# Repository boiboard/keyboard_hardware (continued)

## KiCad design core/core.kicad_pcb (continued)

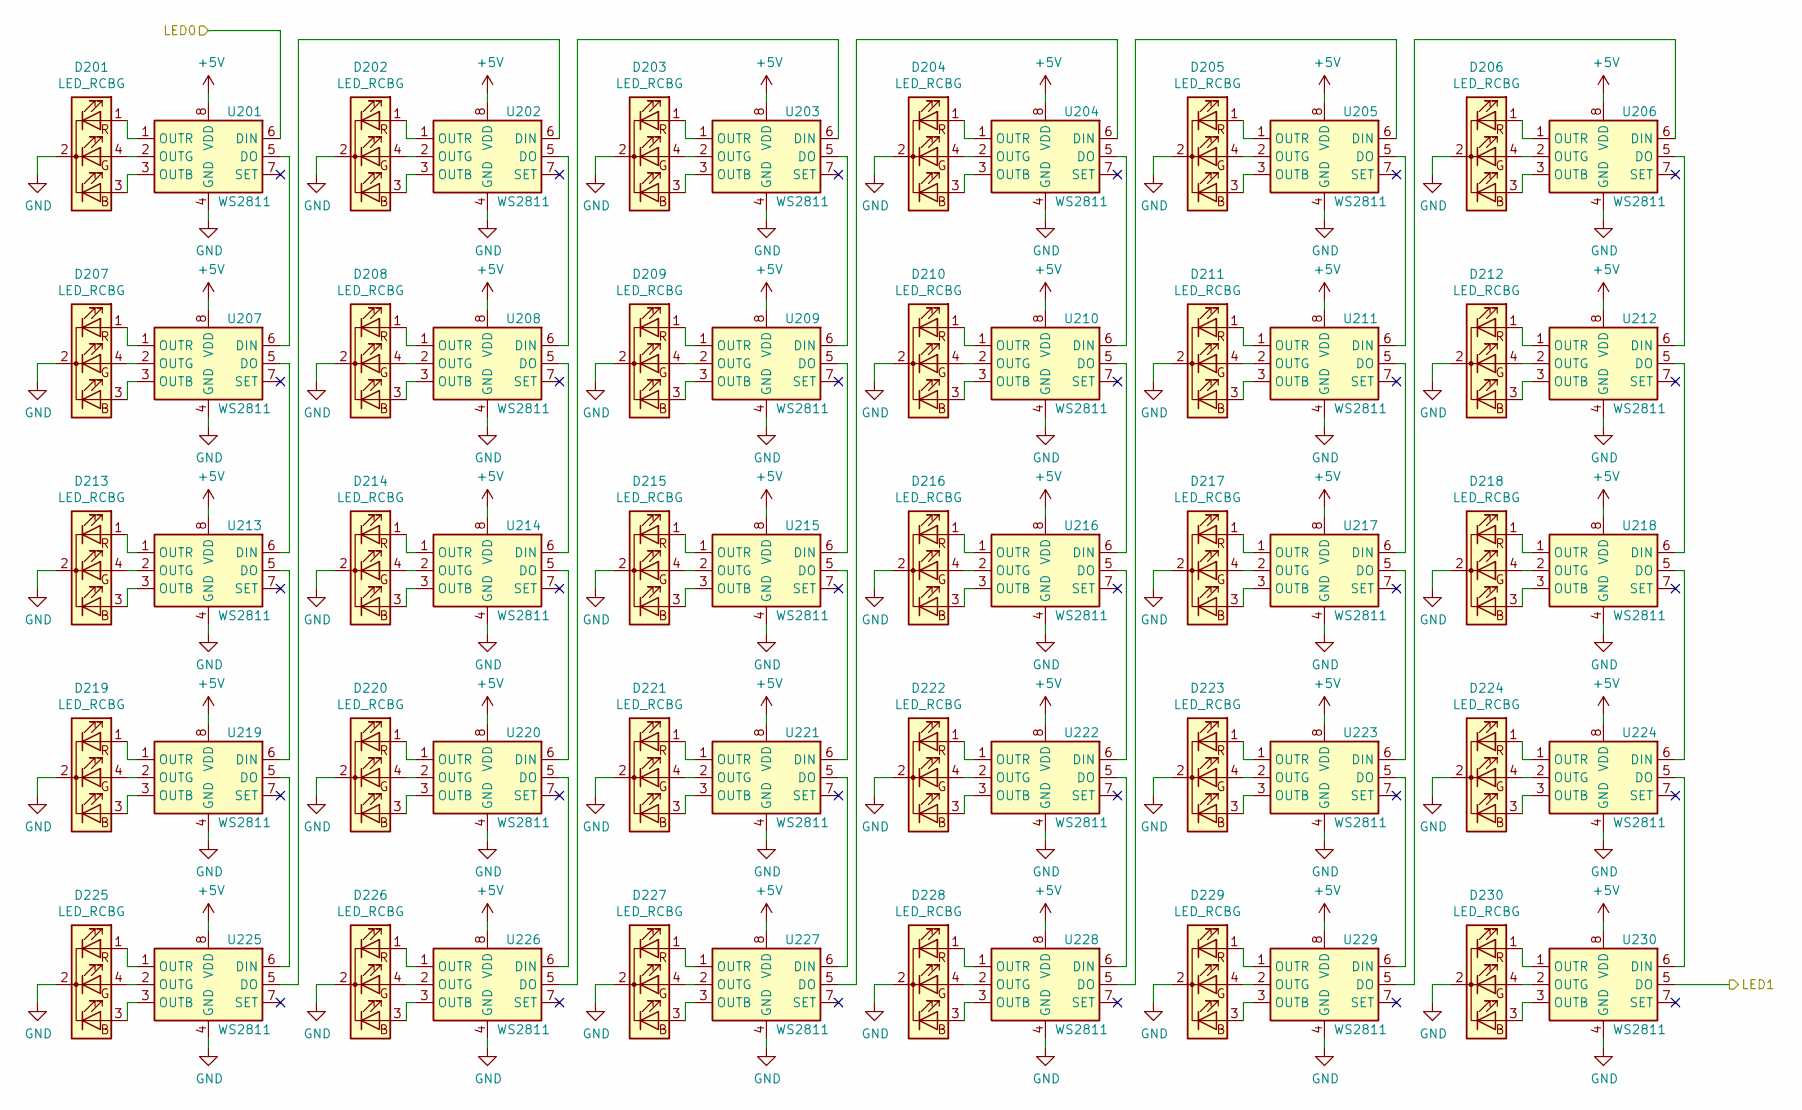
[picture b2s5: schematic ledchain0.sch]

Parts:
D201, D202, D203, D204, D205, D206, D207, D208, D209, D210, D211, D212, D213, D214, D215, D216, D217, D218, D219, D220, D221, D222, D223, D224, D225, D226, D227, D228, D229, D230: LED_RCBG; PinHeader_1x04_P1.00mm_Horizontal
U201, U202, U203, U204, U205, U206, U207, U208, U209, U210, U211, U212, U213, U214, U215, U216, U217, U218, U219, U220, U221, U222, U223, U224, U225, U226, U227, U228, U229, U230: WS2811; SOIC-8-1EP_3.9x4.9mm_P1.27mm_EP2.29x3mm

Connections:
+5V: U201.8 (VDD), U202.8 (VDD), U203.8 (VDD), U204.8 (VDD), U205.8 (VDD), U206.8 (VDD), U207.8 (VDD), U208.8 (VDD), U209.8 (VDD), U210.8 (VDD), U211.8 (VDD), U212.8 (VDD), U213.8 (VDD), U214.8 (VDD), U215.8 (VDD), U216.8 (VDD), U217.8 (VDD), U218.8 (VDD), U219.8 (VDD), U220.8 (VDD), U221.8 (VDD), U222.8 (VDD), U223.8 (VDD), U224.8 (VDD), U225.8 (VDD), U226.8 (VDD), U227.8 (VDD), U228.8 (VDD), U229.8 (VDD), U230.8 (VDD); also elsewhere on the board
/LED0: U201.6 (DIN); also elsewhere on the board
/ledchain0/LED1: U230.5 (DO); also elsewhere on the board
GND: D201.2 (K), D202.2 (K), D203.2 (K), D204.2 (K), D205.2 (K), D206.2 (K), D207.2 (K), D208.2 (K), D209.2 (K), D210.2 (K), D211.2 (K), D212.2 (K), D213.2 (K), D214.2 (K), D215.2 (K), D216.2 (K), D217.2 (K), D218.2 (K), D219.2 (K), D220.2 (K), D221.2 (K), D222.2 (K), D223.2 (K), D224.2 (K), D225.2 (K), D226.2 (K), D227.2 (K), D228.2 (K), D229.2 (K), D230.2 (K), U201.4 (GND), U202.4 (GND), U203.4 (GND), U204.4 (GND), U205.4 (GND), U206.4 (GND), U207.4 (GND), U208.4 (GND), U209.4 (GND), U210.4 (GND), U211.4 (GND), U212.4 (GND), U213.4 (GND), U214.4 (GND), U215.4 (GND), U216.4 (GND), U217.4 (GND), U218.4 (GND), U219.4 (GND), U220.4 (GND), U221.4 (GND), U222.4 (GND), U223.4 (GND), U224.4 (GND), U225.4 (GND), U226.4 (GND), U227.4 (GND), U228.4 (GND), U229.4 (GND), U230.4 (GND); also elsewhere on the board
unnamed: D201.1 (RA), U201.1 (OUTR)
unnamed: D201.3 (BA), U201.3 (OUTB)
unnamed: D201.4 (GA), U201.2 (OUTG)
unnamed: D202.1 (RA), U202.1 (OUTR)
unnamed: D202.3 (BA), U202.3 (OUTB)
unnamed: D202.4 (GA), U202.2 (OUTG)
unnamed: D203.1 (RA), U203.1 (OUTR)
unnamed: D203.3 (BA), U203.3 (OUTB)
unnamed: D203.4 (GA), U203.2 (OUTG)
unnamed: D204.1 (RA), U204.1 (OUTR)
unnamed: D204.3 (BA), U204.3 (OUTB)
unnamed: D204.4 (GA), U204.2 (OUTG)
unnamed: D205.1 (RA), U205.1 (OUTR)
unnamed: D205.3 (BA), U205.3 (OUTB)
unnamed: D205.4 (GA), U205.2 (OUTG)
unnamed: D206.1 (RA), U206.1 (OUTR)
unnamed: D206.3 (BA), U206.3 (OUTB)
unnamed: D206.4 (GA), U206.2 (OUTG)
unnamed: D207.1 (RA), U207.1 (OUTR)
unnamed: D207.3 (BA), U207.3 (OUTB)
unnamed: D207.4 (GA), U207.2 (OUTG)
unnamed: D208.1 (RA), U208.1 (OUTR)
unnamed: D208.3 (BA), U208.3 (OUTB)
unnamed: D208.4 (GA), U208.2 (OUTG)
unnamed: D209.1 (RA), U209.1 (OUTR)
unnamed: D209.3 (BA), U209.3 (OUTB)
unnamed: D209.4 (GA), U209.2 (OUTG)
unnamed: D210.1 (RA), U210.1 (OUTR)
unnamed: D210.3 (BA), U210.3 (OUTB)
unnamed: D210.4 (GA), U210.2 (OUTG)
unnamed: D211.1 (RA), U211.1 (OUTR)
unnamed: D211.3 (BA), U211.3 (OUTB)
unnamed: D211.4 (GA), U211.2 (OUTG)
unnamed: D212.1 (RA), U212.1 (OUTR)
unnamed: D212.3 (BA), U212.3 (OUTB)
unnamed: D212.4 (GA), U212.2 (OUTG)
unnamed: D213.1 (RA), U213.1 (OUTR)
unnamed: D213.3 (BA), U213.3 (OUTB)
unnamed: D213.4 (GA), U213.2 (OUTG)
unnamed: D214.1 (RA), U214.1 (OUTR)
unnamed: D214.3 (BA), U214.3 (OUTB)
unnamed: D214.4 (GA), U214.2 (OUTG)
unnamed: D215.1 (RA), U215.1 (OUTR)
unnamed: D215.3 (BA), U215.3 (OUTB)
unnamed: D215.4 (GA), U215.2 (OUTG)
unnamed: D216.1 (RA), U216.1 (OUTR)
unnamed: D216.3 (BA), U216.3 (OUTB)
unnamed: D216.4 (GA), U216.2 (OUTG)
unnamed: D217.1 (RA), U217.1 (OUTR)
unnamed: D217.3 (BA), U217.3 (OUTB)
unnamed: D217.4 (GA), U217.2 (OUTG)
unnamed: D218.1 (RA), U218.1 (OUTR)
unnamed: D218.3 (BA), U218.3 (OUTB)
unnamed: D218.4 (GA), U218.2 (OUTG)
unnamed: D219.1 (RA), U219.1 (OUTR)
unnamed: D219.3 (BA), U219.3 (OUTB)
unnamed: D219.4 (GA), U219.2 (OUTG)
unnamed: D220.1 (RA), U220.1 (OUTR)
unnamed: D220.3 (BA), U220.3 (OUTB)
unnamed: D220.4 (GA), U220.2 (OUTG)
unnamed: D221.1 (RA), U221.1 (OUTR)
unnamed: D221.3 (BA), U221.3 (OUTB)
unnamed: D221.4 (GA), U221.2 (OUTG)
unnamed: D222.1 (RA), U222.1 (OUTR)
unnamed: D222.3 (BA), U222.3 (OUTB)
unnamed: D222.4 (GA), U222.2 (OUTG)
unnamed: D223.1 (RA), U223.1 (OUTR)
unnamed: D223.3 (BA), U223.3 (OUTB)
unnamed: D223.4 (GA), U223.2 (OUTG)
unnamed: D224.1 (RA), U224.1 (OUTR)
unnamed: D224.3 (BA), U224.3 (OUTB)
unnamed: D224.4 (GA), U224.2 (OUTG)
unnamed: D225.1 (RA), U225.1 (OUTR)
unnamed: D225.3 (BA), U225.3 (OUTB)
unnamed: D225.4 (GA), U225.2 (OUTG)
unnamed: D226.1 (RA), U226.1 (OUTR)
unnamed: D226.3 (BA), U226.3 (OUTB)
unnamed: D226.4 (GA), U226.2 (OUTG)
unnamed: D227.1 (RA), U227.1 (OUTR)
unnamed: D227.3 (BA), U227.3 (OUTB)
unnamed: D227.4 (GA), U227.2 (OUTG)
unnamed: D228.1 (RA), U228.1 (OUTR)
unnamed: D228.3 (BA), U228.3 (OUTB)
unnamed: D228.4 (GA), U228.2 (OUTG)
unnamed: D229.1 (RA), U229.1 (OUTR)
unnamed: D229.3 (BA), U229.3 (OUTB)
unnamed: D229.4 (GA), U229.2 (OUTG)
unnamed: D230.1 (RA), U230.1 (OUTR)
unnamed: D230.3 (BA), U230.3 (OUTB)
unnamed: D230.4 (GA), U230.2 (OUTG)
unnamed: U201.5 (DO), U207.6 (DIN)
unnamed: U202.5 (DO), U208.6 (DIN)
unnamed: U202.6 (DIN), U225.5 (DO)
unnamed: U203.5 (DO), U209.6 (DIN)
unnamed: U203.6 (DIN), U226.5 (DO)
unnamed: U204.5 (DO), U210.6 (DIN)
unnamed: U204.6 (DIN), U227.5 (DO)
unnamed: U205.5 (DO), U211.6 (DIN)
unnamed: U205.6 (DIN), U228.5 (DO)
unnamed: U206.5 (DO), U212.6 (DIN)
unnamed: U206.6 (DIN), U229.5 (DO)
unnamed: U207.5 (DO), U213.6 (DIN)
unnamed: U208.5 (DO), U214.6 (DIN)
unnamed: U209.5 (DO), U215.6 (DIN)
unnamed: U210.5 (DO), U216.6 (DIN)
unnamed: U211.5 (DO), U217.6 (DIN)
unnamed: U212.5 (DO), U218.6 (DIN)
unnamed: U213.5 (DO), U219.6 (DIN)
unnamed: U214.5 (DO), U220.6 (DIN)
unnamed: U215.5 (DO), U221.6 (DIN)
unnamed: U216.5 (DO), U222.6 (DIN)
unnamed: U217.5 (DO), U223.6 (DIN)
unnamed: U218.5 (DO), U224.6 (DIN)
unnamed: U219.5 (DO), U225.6 (DIN)
unnamed: U220.5 (DO), U226.6 (DIN)
unnamed: U221.5 (DO), U227.6 (DIN)
unnamed: U222.5 (DO), U228.6 (DIN)
unnamed: U223.5 (DO), U229.6 (DIN)
unnamed: U224.5 (DO), U230.6 (DIN)

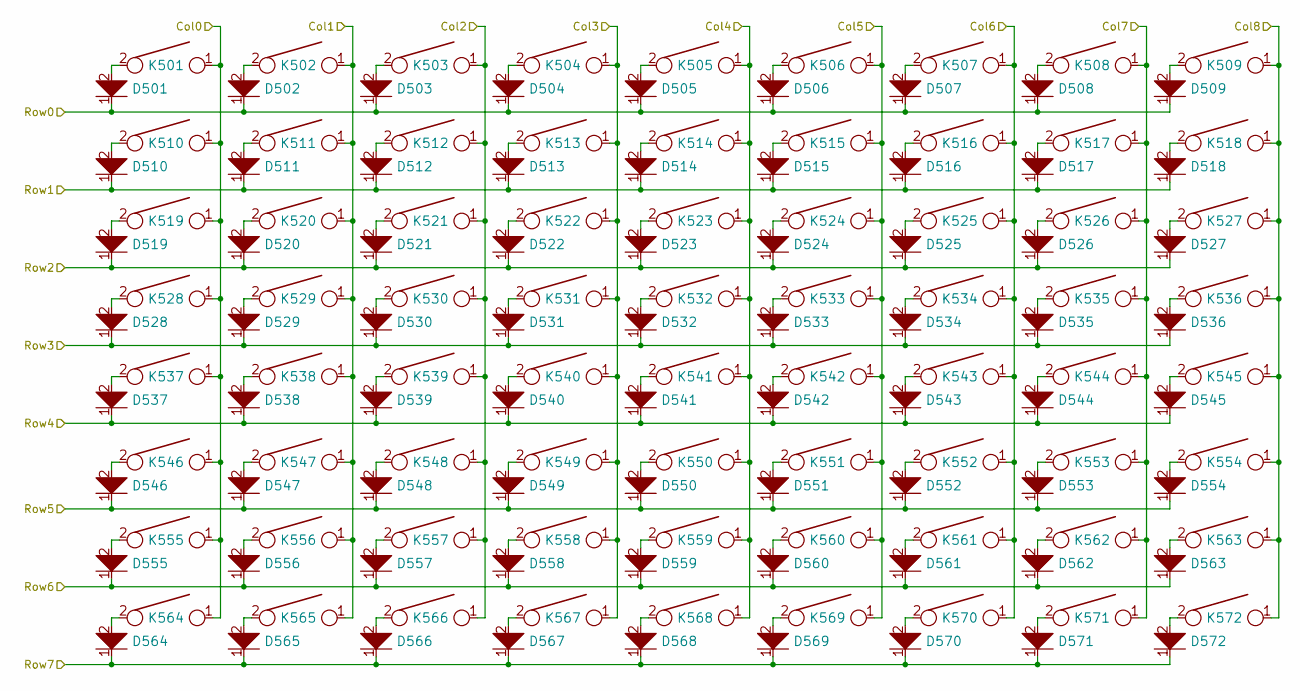
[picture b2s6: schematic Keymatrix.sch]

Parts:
D501, D502, D503, D504, D505, D506, D507, D508, D509, D510, D511, D512, D513, D514, D515, D516, D517, D518, D519, D520, D521, D522, D523, D524, D525, D526, D527, D528, D529, D530, D531, D532, D533, D534, D535, D536, D537, D538, D539, D540, D541, D542, D543, D544, D545, D546, D547, D548, D549, D550, D551, D552, D553, D554, D555, D556, D557, D558, D559, D560, D561, D562, D563, D564, D565, D566, D567, D568, D569, D570, D571, D572: D; D_SOD123_axial
K501, K502, K503, K504, K505, K506, K507, K508, K509, K510, K511, K512, K513, K514, K515, K516, K517, K518, K519, K520, K521, K522, K523, K524, K525, K526, K527, K528, K529, K530, K531, K532, K533, K534, K535, K536, K537, K538, K539, K540, K541, K542, K543, K544, K545, K546, K547, K548, K549, K550, K551, K552, K553, K554, K555, K556, K557, K558, K559, K560, K561, K562, K563, K564, K565, K566, K567, K568, K569, K570, K571, K572: KEYSW; Kailh_socket

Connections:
/Col0: K501.1, K510.1, K519.1, K528.1, K537.1, K546.1, K555.1, K564.1; also elsewhere on the board
/Col1: K502.1, K511.1, K520.1, K529.1, K538.1, K547.1, K556.1, K565.1; also elsewhere on the board
/Col2: K503.1, K512.1, K521.1, K530.1, K539.1, K548.1, K557.1, K566.1; also elsewhere on the board
/Col3: K504.1, K513.1, K522.1, K531.1, K540.1, K549.1, K558.1, K567.1; also elsewhere on the board
/Col4: K505.1, K514.1, K523.1, K532.1, K541.1, K550.1, K559.1, K568.1; also elsewhere on the board
/Col5: K506.1, K515.1, K524.1, K533.1, K542.1, K551.1, K560.1, K569.1; also elsewhere on the board
/Col6: K507.1, K516.1, K525.1, K534.1, K543.1, K552.1, K561.1, K570.1; also elsewhere on the board
/Col7: K508.1, K517.1, K526.1, K535.1, K544.1, K553.1, K562.1, K571.1; also elsewhere on the board
/Col8: K509.1, K518.1, K527.1, K536.1, K545.1, K554.1, K563.1, K572.1; also elsewhere on the board
/Row0: D501.1, D502.1, D503.1, D504.1, D505.1, D506.1, D507.1, D508.1, D509.1; also elsewhere on the board
/Row1: D510.1, D511.1, D512.1, D513.1, D514.1, D515.1, D516.1, D517.1, D518.1; also elsewhere on the board
/Row2: D519.1, D520.1, D521.1, D522.1, D523.1, D524.1, D525.1, D526.1, D527.1; also elsewhere on the board
/Row3: D528.1, D529.1, D530.1, D531.1, D532.1, D533.1, D534.1, D535.1, D536.1; also elsewhere on the board
/Row4: D537.1, D538.1, D539.1, D540.1, D541.1, D542.1, D543.1, D544.1, D545.1; also elsewhere on the board
/Row5: D546.1, D547.1, D548.1, D549.1, D550.1, D551.1, D552.1, D553.1, D554.1; also elsewhere on the board
/Row6: D555.1, D556.1, D557.1, D558.1, D559.1, D560.1, D561.1, D562.1, D563.1; also elsewhere on the board
/Row7: D564.1, D565.1, D566.1, D567.1, D568.1, D569.1, D570.1, D571.1, D572.1; also elsewhere on the board
unnamed: D501.2, K501.2
unnamed: D502.2, K502.2
unnamed: D503.2, K503.2
unnamed: D504.2, K504.2
unnamed: D505.2, K505.2
unnamed: D506.2, K506.2
unnamed: D507.2, K507.2
unnamed: D508.2, K508.2
unnamed: D509.2, K509.2
unnamed: D510.2, K510.2
unnamed: D511.2, K511.2
unnamed: D512.2, K512.2
unnamed: D513.2, K513.2
unnamed: D514.2, K514.2
unnamed: D515.2, K515.2
unnamed: D516.2, K516.2
unnamed: D517.2, K517.2
unnamed: D518.2, K518.2
unnamed: D519.2, K519.2
unnamed: D520.2, K520.2
unnamed: D521.2, K521.2
unnamed: D522.2, K522.2
unnamed: D523.2, K523.2
unnamed: D524.2, K524.2
unnamed: D525.2, K525.2
unnamed: D526.2, K526.2
unnamed: D527.2, K527.2
unnamed: D528.2, K528.2
unnamed: D529.2, K529.2
unnamed: D530.2, K530.2
unnamed: D531.2, K531.2
unnamed: D532.2, K532.2
unnamed: D533.2, K533.2
unnamed: D534.2, K534.2
unnamed: D535.2, K535.2
unnamed: D536.2, K536.2
unnamed: D537.2, K537.2
unnamed: D538.2, K538.2
unnamed: D539.2, K539.2
unnamed: D540.2, K540.2
unnamed: D541.2, K541.2
unnamed: D542.2, K542.2
unnamed: D543.2, K543.2
unnamed: D544.2, K544.2
unnamed: D545.2, K545.2
unnamed: D546.2, K546.2
unnamed: D547.2, K547.2
unnamed: D548.2, K548.2
unnamed: D549.2, K549.2
unnamed: D550.2, K550.2
unnamed: D551.2, K551.2
unnamed: D552.2, K552.2
unnamed: D553.2, K553.2
unnamed: D554.2, K554.2
unnamed: D555.2, K555.2
unnamed: D556.2, K556.2
unnamed: D557.2, K557.2
unnamed: D558.2, K558.2
unnamed: D559.2, K559.2
unnamed: D560.2, K560.2
unnamed: D561.2, K561.2
unnamed: D562.2, K562.2
unnamed: D563.2, K563.2
unnamed: D564.2, K564.2
unnamed: D565.2, K565.2
unnamed: D566.2, K566.2
unnamed: D567.2, K567.2
unnamed: D568.2, K568.2
unnamed: D569.2, K569.2
unnamed: D570.2, K570.2
unnamed: D571.2, K571.2
unnamed: D572.2, K572.2

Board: 2 copper layers, 288 parts (0 on the bottom side), 377 nets, no tracks yet.

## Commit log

2019-10-24 add files
2019-10-24 update schematic
2019-10-25 hopefully this fixed libraries, nextcloud has been getting mad
2019-10-25 add core project
2019-10-25 finish keymatrix and assign footprints
2019-10-25 add an RGB controller to core
2019-10-25 work on rgb stuff
2019-10-27 add addressable LED info
2019-10-27 update schematic with more addressable stuff
2019-10-28 add sources for LEDs and wire some in score schematic
2019-10-28 investigate 3mm rgb leds
2019-10-28 add controllers and 3mm RGB LEDs
2019-10-28 update to teensy LC
2019-10-29 add aliexpress supplier for led
2019-10-29 add schematic row of new LED design
2019-10-30 Cleared out non-submodule libraries
2019-10-30 Added libraries as submodules.
2019-10-30 Added libraries to the project.
2019-10-30 use symbols for LED power/ground
2019-10-30 change submodules to https format
2019-10-30 Removed schematic backup from git
2019-10-30 Added initial git ignore
2019-10-30 Changed pin assignments, cleaned up RGB LEDs
2019-10-30 LED chain of horrors
2019-10-30 add new sheet for keymatrix, rearrange keymatrix, resize sheets
2019-10-30 move LEDs into their own sheets
2019-10-30 annotate led chain
2019-10-30 remove example LED and controller
2019-10-30 start key layout
2019-10-30 remove useless subdir
2019-10-30 Added possible key matrix encoding alternative
2019-10-30 Added project library
2019-10-30 Added NOR gate to shift register input to create a ring counter
2019-10-30 Added more backup types to gitignore
2019-10-30 Changed encoder to CD4532B, removed inverters
2019-10-30 Fixed ERC errors and initially populated board
2019-10-31 separate footprints on PCB and put some diodes with their keyswitches
2019-11-01 Initial board layout for the 4x4 test board
2019-11-01 Updated LED footprints
2019-11-03 clean up supplier links
2019-11-03 add suppliers
2019-11-04 clean up datasheets folder
2019-11-12 add led socket footprint
2019-12-01 remove through hole leds
2019-12-01 remove through hole LED datasheets
2019-12-01 add datasheets for smd leds
2019-12-02 add supplier
2019-12-02 update test board schematic to SMD LED
2019-12-04 example routing for new LED part
2019-12-05 update schematic to CRGB LEDs and move footprints on pcb
2019-12-23 update schematic to smd diode
2019-12-24 example on pcb of how diodes might go
2019-12-30 change some file names to be friendlier
2021-03-14 Create plate and case builder
